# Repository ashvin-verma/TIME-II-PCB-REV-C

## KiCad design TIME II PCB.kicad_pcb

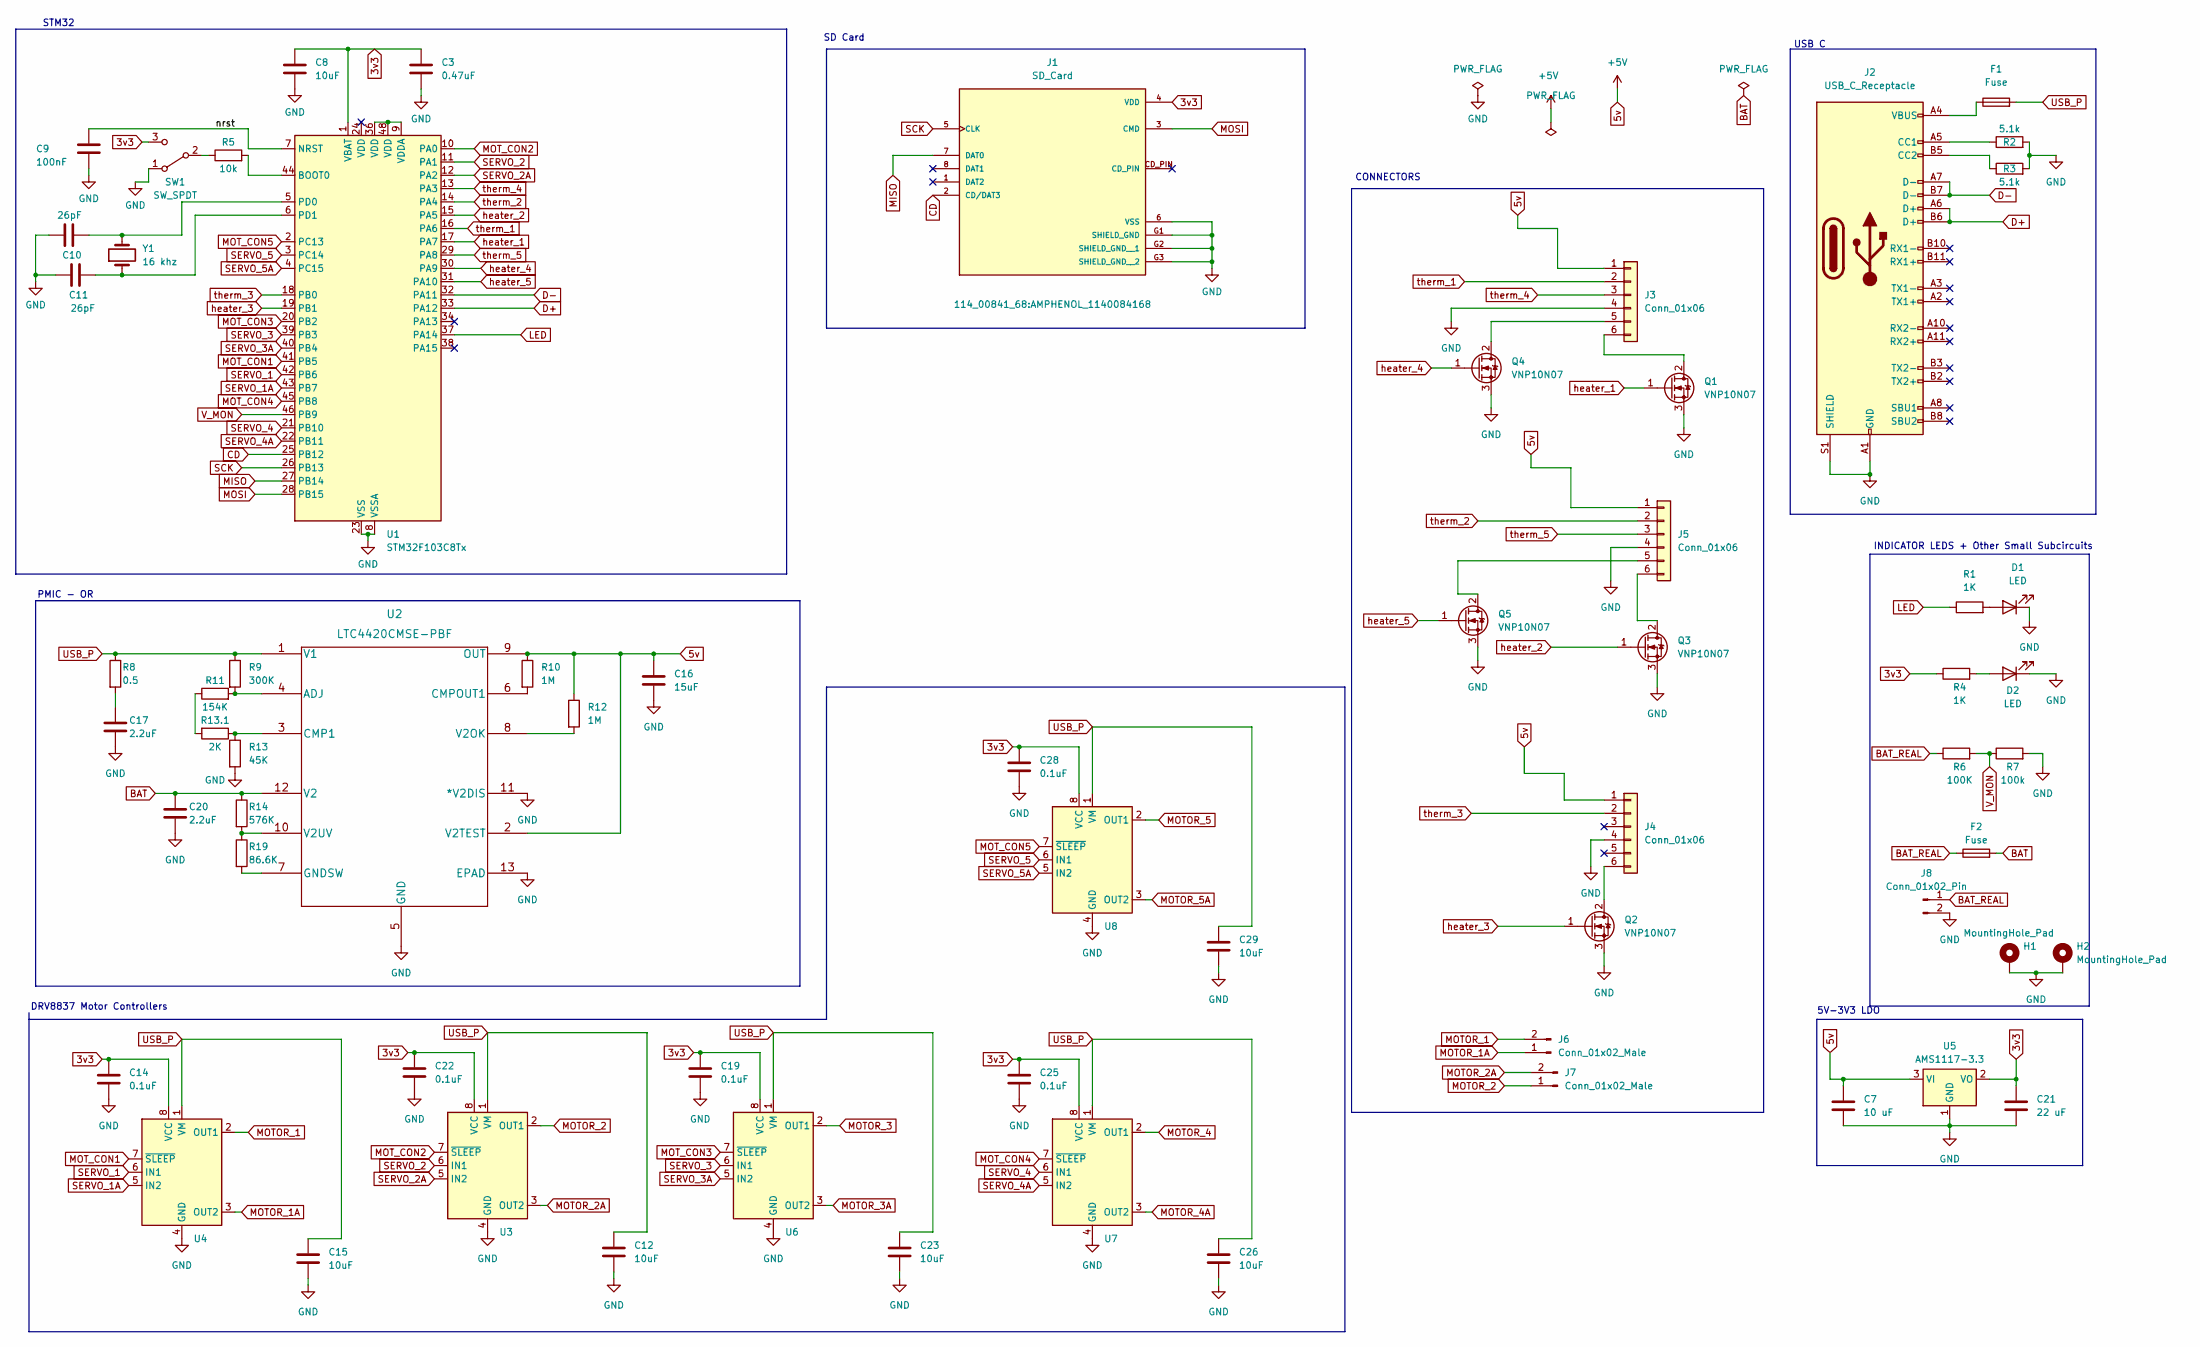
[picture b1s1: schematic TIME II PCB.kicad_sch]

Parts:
C3: 0.47uF; C_0402_1005Metric
C7: 10 uF; C_0402_1005Metric
C8, C12, C15, C23, C26, C29: 10uF; C_0402_1005Metric
C9: 100nF; C_0402_1005Metric
C10, C11: 26pF; C_0402_1005Metric
C14, C19, C22, C25, C28: 0.1uF; C_0402_1005Metric
C16: 15uF; C_0402_1005Metric
C17, C20: 2.2uF; C_0402_1005Metric
C21: 22 uF; C_0402_1005Metric
D1, D2: LED; LED_0603_1608Metric
F1, F2: Fuse; Fuse_0603_1608Metric
H1, H2: MountingHole_Pad; MountingHole_2.5mm_Pad
J1: SD_Card; AMPHENOL_1140084168; PARTREV F
J2: USB_C_Receptacle; USB4105-GF-A
J3, J4, J5: Conn_01x06; CON_525590652_MOL
J6, J7: Conn_01x02_Male; JST_XH_B2B-XH-A_1x02_P2.50mm_Vertical
J8: Conn_01x02_Pin; JST_XH_B2B-XH-AM_1x02_P2.50mm_Vertical
Q1, Q2, Q3, Q4, Q5: VNP10N07; SOT-23-3
R1, R4: 1K; R_0402_1005Metric
R2, R3: 5.1k; R_0402_1005Metric
R5: 10k; R_0402_1005Metric
R6: 100K; R_0402_1005Metric
R7: 100k; R_0402_1005Metric
R8: 0.5; R_0402_1005Metric
R9: 300K; R_0603_1608Metric
R10, R12: 1M; R_0402_1005Metric
R11: 2K; R_0603_1608Metric
R13: 45K; R_0603_1608Metric
R13.1: 154K; R_0603_1608Metric
R14: 576K; R_0402_1005Metric
R19: 86.6K; R_0402_1005Metric
SW1: SW_SPDT; PinHeader_1x03_P1.27mm_Vertical
U1: STM32F103C8Tx; LQFP-48_7x7mm_P0.5mm
U2: LTC4420CMSE-PBF; MSOP-12-1EP_3x4mm_P0.65mm_EP1.65x2.85mm
U3, U4, U6, U7, U8: WSON-8-1EP_2x2mm_P0.5mm_EP0.9x1.6mm_ThermalVias
U5: AMS1117-3.3; SOT-223-3_TabPin2
Y1: 16 khz; abm3

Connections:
3v3: C3.1, C8.1, C14.1, C19.1, C21.1, C22.1, C25.1, C28.1, J1.4 (VDD), R4.1, SW1.3 (C), U1.1 (VBAT), U3.8 (VCC), U4.8 (VCC), U5.2 (VO), U6.8 (VCC), U7.8 (VCC), U8.8 (VCC); also elsewhere on the board
5v: C7.1, C16.1, J3.1, J4.1, J5.1, R10.1, R12.1, U2.2 (V2TEST), U2.9 (OUT), U5.3 (VI)
/nrst: C9.1, U1.7 (NRST)
BAT: C20.1, F2.2, R14.1, U2.12 (V2)
BAT_REAL: F2.1, J8.1, R6.1
CD: J1.2 (CD/DAT3), U1.25 (PB12)
D+: J2.A6 (D+), J2.B6 (D+), U1.33 (PA12)
D-: J2.A7 (D-), J2.B7 (D-), U1.32 (PA11)
GND: C3.2, C7.2, C8.2, C9.2, C10.1, C11.1, C12.2, C14.2, C15.2, C16.2, C17.2, C19.2, C20.2, C21.2, C22.2, C23.2, C25.2, C26.2, C28.2, C29.2, D1.1 (K), D2.1 (K), H1.1, H2.1, J1.6 (VSS), J1.G1 (SHIELD_GND), J1.G2 (SHIELD_GND__1), J1.G3 (SHIELD_GND__2), J2.A1 (GND), J2.A12 (GND), J2.B1 (GND), J2.B12 (GND), J2.S1 (SHIELD), J3.4, J4.4, J5.4, J8.2, Q1.3 (S), Q2.3 (S), Q3.3 (S), Q4.3 (S), Q5.3 (S), R2.2, R3.2, R7.2, R13.2, SW1.1 (A), U1.8 (VSSA), U1.23 (VSS), U1.35 (VSS), U1.47 (VSS), U2.5 (GND), U2.11 (*V2DIS), U2.13 (EPAD), U3.4 (GND), U3.9 (GND), U4.4 (GND), U4.9 (GND), U5.1 (GND), U6.4 (GND), U6.9 (GND), U7.4 (GND), U7.9 (GND), U8.4 (GND), U8.9 (GND); also elsewhere on the board
LED: R1.1, U1.37 (PA14)
MISO: J1.7 (DAT0), U1.27 (PB14)
MOSI: J1.3 (CMD), U1.28 (PB15)
MOTOR_1: J6.2, U4.2 (OUT1)
MOTOR_1A: J6.1, U4.3 (OUT2)
MOTOR_2: J7.1, U3.2 (OUT1)
MOTOR_2A: J7.2, U3.3 (OUT2)
MOTOR_3: U6.2 (OUT1)
MOTOR_3A: U6.3 (OUT2)
MOTOR_4: U7.2 (OUT1)
MOTOR_4A: U7.3 (OUT2)
MOTOR_5: U8.2 (OUT1)
MOTOR_5A: U8.3 (OUT2)
MOT_CON1: U1.41 (PB5), U4.7 (~SLEEP)
MOT_CON2: U1.10 (PA0), U3.7 (~SLEEP)
MOT_CON3: U1.20 (PB2), U6.7 (~SLEEP)
MOT_CON4: U1.45 (PB8), U7.7 (~SLEEP)
MOT_CON5: U1.2 (PC13), U8.7 (~SLEEP)
unnamed: C17.1, R8.2
unnamed: D1.2 (A), R1.2
unnamed: D2.2 (A), R4.2
unnamed: F1.1, J2.A4 (VBUS), J2.A9 (VBUS), J2.B4 (VBUS), J2.B9 (VBUS)
unnamed: J2.A5 (CC1), R2.1
unnamed: J2.B5 (CC2), R3.1
unnamed: J3.5, Q4.2 (D)
unnamed: J3.6, Q1.2 (D)
unnamed: J4.6, Q2.2 (D)
unnamed: J5.5, Q5.2 (D)
unnamed: J5.6, Q3.2 (D)
unnamed: R11.1, R13.1.2
unnamed: R5.1, SW1.2 (B)
unnamed: R5.2, U1.44 (BOOT0)
unnamed: C10.2, U1.5 (PD0), Y1.2
unnamed: C11.2, U1.6 (PD1), Y1.1
unnamed: U1.9 (VDDA), U1.36 (VDD), U1.48 (VDD)
unnamed: R9.2, R11.2, U2.4 (ADJ)
unnamed: R13.1, R13.1.1, U2.3 (CMP1)
unnamed: R10.2, U2.6 (CMPOUT1)
unnamed: R19.2, U2.7 (GNDSW)
unnamed: R12.2, U2.8 (V2OK)
unnamed: R14.2, R19.1, U2.10 (V2UV)
SCK: J1.5 (CLK), U1.26 (PB13)
SERVO_1: U1.42 (PB6), U4.6 (IN1)
SERVO_1A: U1.43 (PB7), U4.5 (IN2)
SERVO_2: U1.11 (PA1), U3.6 (IN1)
SERVO_2A: U1.12 (PA2), U3.5 (IN2)
SERVO_3: U1.39 (PB3), U6.6 (IN1)
SERVO_3A: U1.40 (PB4), U6.5 (IN2)
SERVO_4: U1.21 (PB10), U7.6 (IN1)
SERVO_4A: U1.22 (PB11), U7.5 (IN2)
SERVO_5: U1.3 (PC14), U8.6 (IN1)
SERVO_5A: U1.4 (PC15), U8.5 (IN2)
USB_P: C12.1, C15.1, C23.1, C26.1, C29.1, F1.2, R8.1, R9.1, U2.1 (V1), U3.1 (VM), U4.1 (VM), U6.1 (VM), U7.1 (VM), U8.1 (VM); also elsewhere on the board
V_MON: R6.2, R7.1, U1.46 (PB9)
heater_1: Q1.1 (G), U1.17 (PA7)
heater_2: Q3.1 (G), U1.15 (PA5)
heater_3: Q2.1 (G), U1.19 (PB1)
heater_4: Q4.1 (G), U1.30 (PA9)
heater_5: Q5.1 (G), U1.31 (PA10)
therm_1: J3.2, U1.16 (PA6)
therm_2: J5.2, U1.14 (PA4)
therm_3: J4.2, U1.18 (PB0)
therm_4: J3.3, U1.13 (PA3)
therm_5: J5.3, U1.29 (PA8)

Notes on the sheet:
DRV8837 Motor Controllers
INDICATOR LEDS + Other Small Subcircuits
STM32
SD Card
PMIC - OR
USB C
5V-3V3 LDO
CONNECTORS

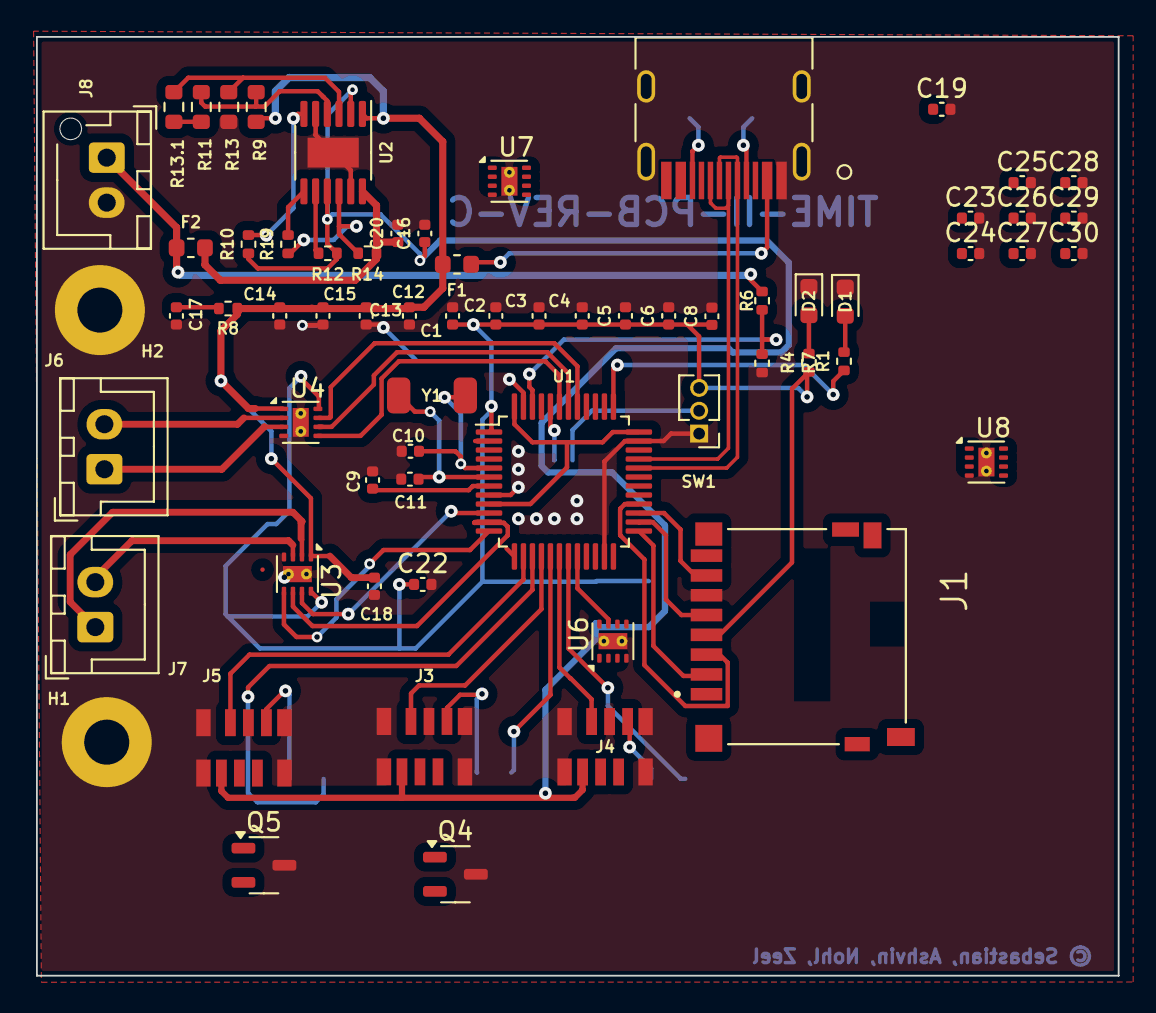
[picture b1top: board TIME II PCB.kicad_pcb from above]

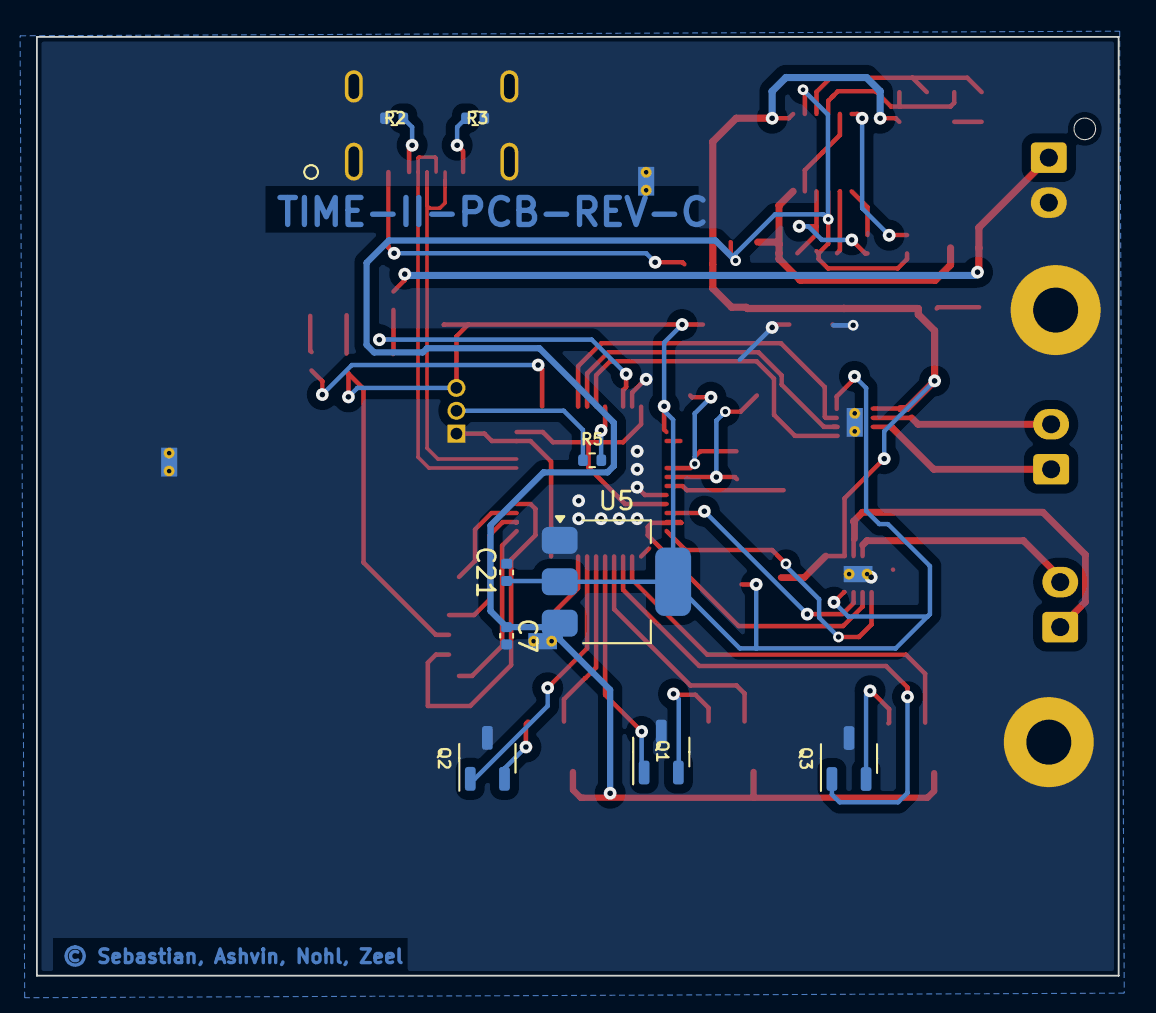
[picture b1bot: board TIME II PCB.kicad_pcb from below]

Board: 4 copper layers, 60.1 x 52.2 mm, 75 parts (9 on the bottom side), 67 nets.

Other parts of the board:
C1, C2, C4, C5: 100nF; C_0402_1005Metric
C6: 10nF; C_0402_1005Metric
C13, C18, C24, C27, C30: 0.01uF; C_0402_1005Metric

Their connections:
3v3: C1.1, C2.1, C4.1, C5.1, C6.1; also elsewhere on the board
GND: C1.2, C2.2, C4.2, C5.2, C6.2, C13.2, C18.2, C24.2, C27.2, C30.2; also elsewhere on the board
USB_P: C13.1, C18.1, C24.1, C27.1, C30.1; also elsewhere on the board

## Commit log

2024-10-11 erc fixes
2024-10-13 pre new motor driver symbol/footprint
2024-10-13 updating the motor controller symbol/footprint
2024-10-25 5 motors, 5 heaters, 5 thermistors mod
2024-10-25 changed capacitors out
2024-10-25 changed to 4 layer

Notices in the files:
TIME II PCB.kicad_pcb:
© Sebastian, Ashvin, Nohl, Zeel
parts and their libraries:
Copyright 2021 Accelerated Designs. All rights reserved.
